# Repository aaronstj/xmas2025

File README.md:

# xmas2025

This is the code and schematics/PCB design for the 2025 Christmas ornament.

The ornament runs on an ATTINY85 microcontroller running the Micronucleus bootloader.  The code runs on the Arduino platform using the ATTinyCore.

## The top of the ornament looks like a USB?
It is! You can reprogram the ornament through the usb.  Download the ATTinyCore for Arduino, set your board to "ATTiny85 (Micronucleus/Digispark)".  When uploading new code, insert the ESB end of the ornament into your USB port, component-side up - it's not quite the same right size, so it may take some wiggling and careful holding.  You will likely need to use `Zadig` to install the `libusbK` driver.

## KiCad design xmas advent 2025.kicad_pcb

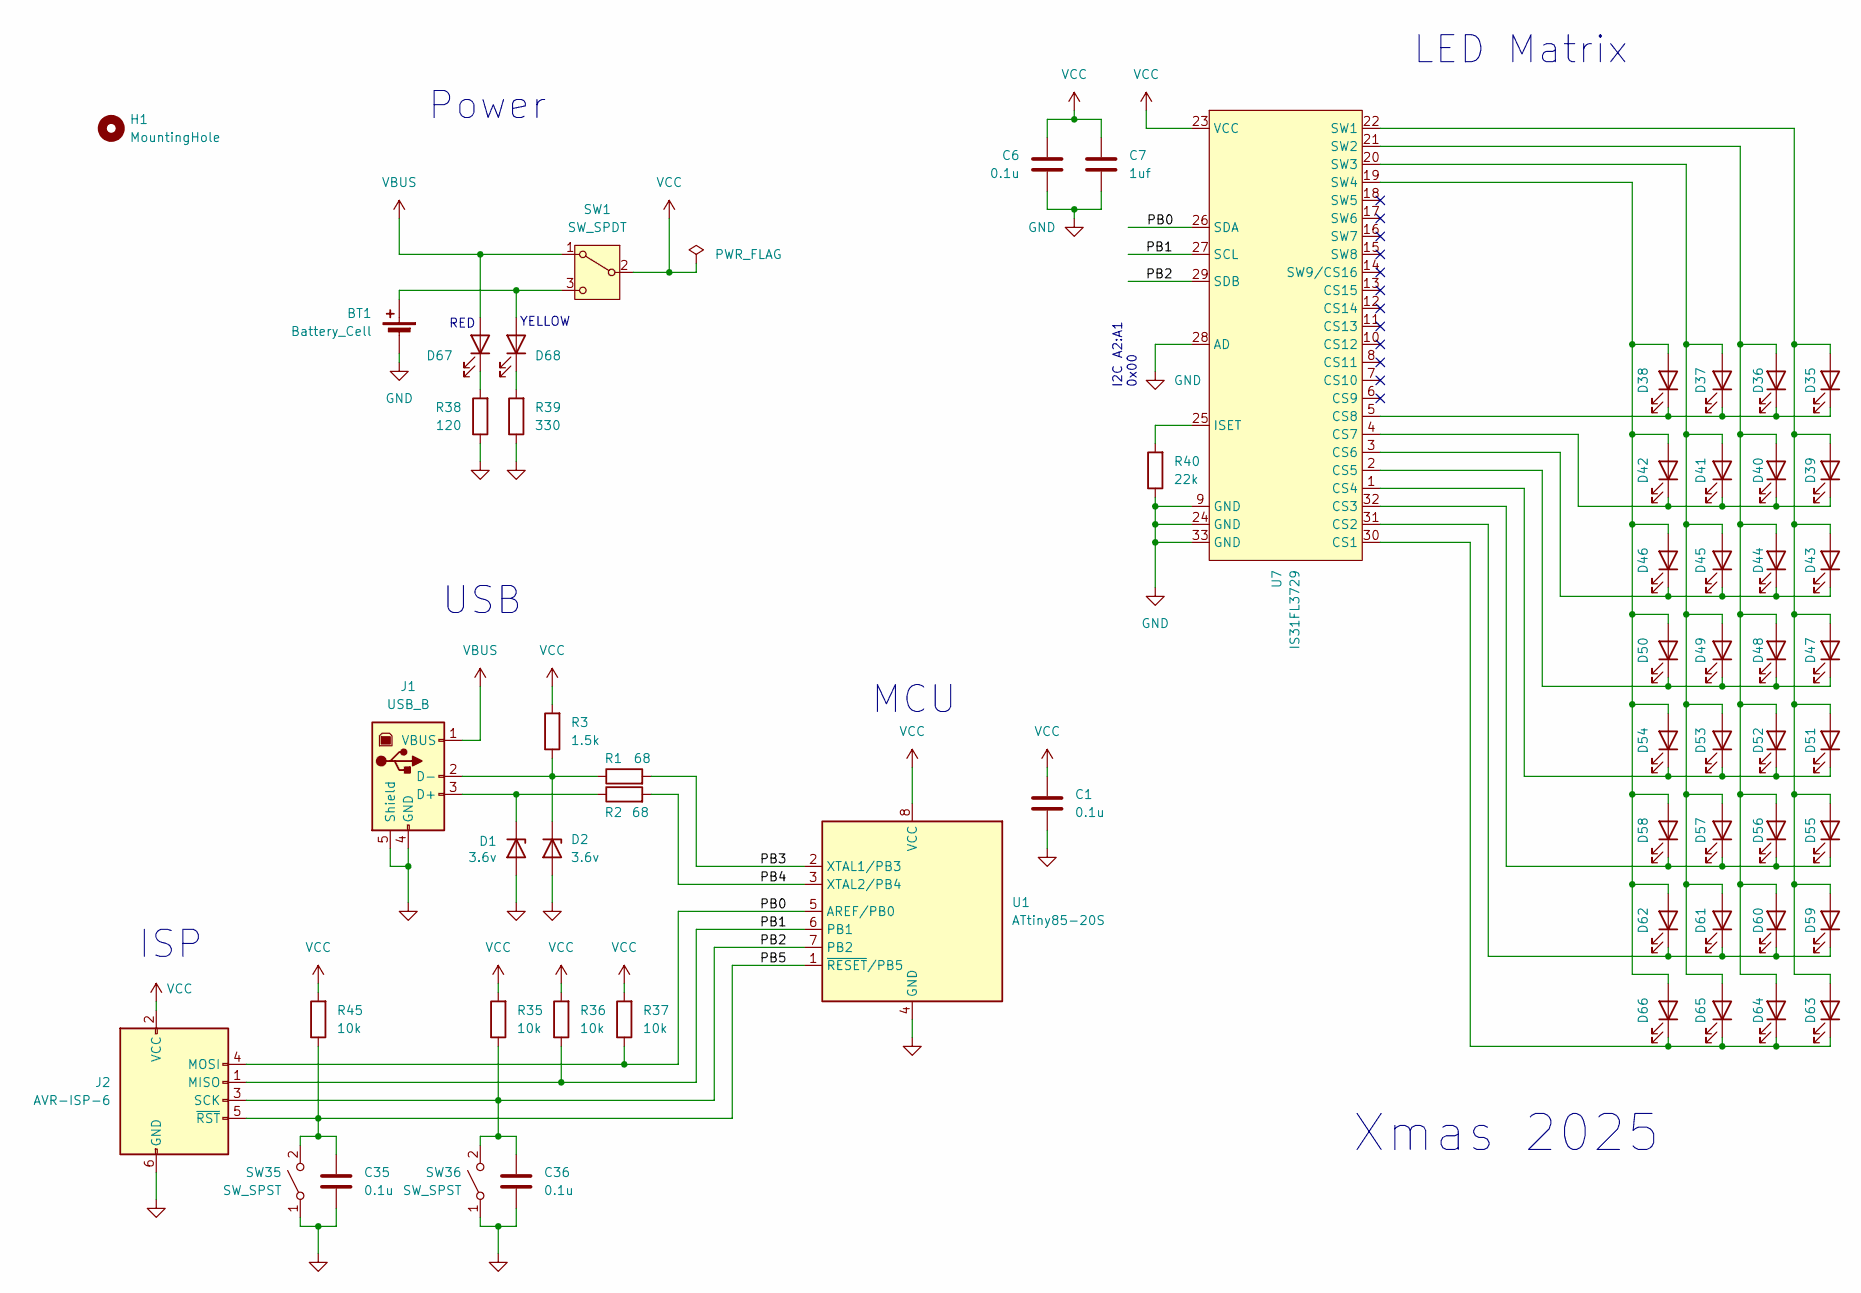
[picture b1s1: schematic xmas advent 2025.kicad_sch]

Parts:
BT1: Battery_Cell; BATTCOM_20MM_PTH
C1, C6, C35, C36: 0.1u; C_0402_1005Metric
C7: 1uf; C_0402_1005Metric
D1, D2: 3.6v; D_SOD-123
D35, D36, D37, D38, D39, D40, D41, D42, D43, D44, D45, D46, D47, D48, D49, D50, D51, D52, D53, D54, D55, D56, D57, D58, D59, D60, D61, D62, D63, D64, D65, D66: LED; LED_0805_2012Metric
D67: RED; LED_0603_1608Metric
D68: Yellow; LED_0603_1608Metric
H1: MountingHole; MountingHole_3mm
J1: USB_B; CONN-USB-A-PCB-TRACES
J2: AVR-ISP-6; PinHeader_2x03_P2.54mm_Vertical
R1, R2: 68; R_0402_1005Metric
R3: 1.5k; R_0402_1005Metric
R35, R36, R37, R45: 10k; R_0402_1005Metric
R38: 120; R_0402_1005Metric
R39: 330; R_0402_1005Metric
R40: 22k; R_0402_1005Metric
SW1: SW_SPDT; SW_500SSP1S2M2QEA
SW35, SW36: SW_SPST; SW_Push_1P1T_XKB_TS-1187A
U1: ATtiny85-20S; SOIC-8W_5.3x5.3mm_P1.27mm
U7: IS31FL3729; QFN-32-1EP_4x4mm_P0.4mm_EP2.65x2.65mm_ThermalVias

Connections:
/PB0: J2.4 (MOSI), R37.1, U1.5 (AREF/PB0), U7.26 (SDA)
/PB1: J2.1 (MISO), R36.1, U1.6 (PB1), U7.27 (SCL)
/PB2: C36.1, J2.3 (SCK), R35.1, SW36.2 (B), U1.7 (PB2), U7.29 (SDB)
/PB3: R1.2, U1.2 (XTAL1/PB3)
/PB4: R2.2, U1.3 (XTAL2/PB4)
/PB5: C35.1, J2.5 (~RST), R45.1, SW35.2 (B), U1.1 (~RESET/PB5)
GND: BT1.2 (-), C1.2, C6.1, C7.2, C35.2, C36.2, D1.2 (A), D2.2 (A), J1.4 (GND), J1.5 (Shield), J2.6 (GND), R38.1, R39.1, R40.1, SW35.1 (A), SW36.1 (A), U1.4 (GND), U7.9 (GND), U7.24 (GND), U7.28 (AD), U7.33 (GND)
unnamed: BT1.1 (+), D68.2 (A), SW1.3 (C)
unnamed: D1.1 (K), J1.3 (D+), R2.1
unnamed: D2.1 (K), J1.2 (D-), R1.1, R3.1
unnamed: D35.2 (A), D39.2 (A), D43.2 (A), D47.2 (A), D51.2 (A), D55.2 (A), D59.2 (A), D63.2 (A), U7.22 (SW1)
unnamed: D35.1 (K), D36.1 (K), D37.1 (K), D38.1 (K), U7.5 (CS8)
unnamed: D36.2 (A), D40.2 (A), D44.2 (A), D48.2 (A), D52.2 (A), D56.2 (A), D60.2 (A), D64.2 (A), U7.21 (SW2)
unnamed: D37.2 (A), D41.2 (A), D45.2 (A), D49.2 (A), D53.2 (A), D57.2 (A), D61.2 (A), D65.2 (A), U7.20 (SW3)
unnamed: D38.2 (A), D42.2 (A), D46.2 (A), D50.2 (A), D54.2 (A), D58.2 (A), D62.2 (A), D66.2 (A), U7.19 (SW4)
unnamed: D39.1 (K), D40.1 (K), D41.1 (K), D42.1 (K), U7.4 (CS7)
unnamed: D43.1 (K), D44.1 (K), D45.1 (K), D46.1 (K), U7.3 (CS6)
unnamed: D47.1 (K), D48.1 (K), D49.1 (K), D50.1 (K), U7.2 (CS5)
unnamed: D51.1 (K), D52.1 (K), D53.1 (K), D54.1 (K), U7.1 (CS4)
unnamed: D55.1 (K), D56.1 (K), D57.1 (K), D58.1 (K), U7.32 (CS3)
unnamed: D59.1 (K), D60.1 (K), D61.1 (K), D62.1 (K), U7.31 (CS2)
unnamed: D63.1 (K), D64.1 (K), D65.1 (K), D66.1 (K), U7.30 (CS1)
unnamed: D67.1 (K), R38.2
unnamed: D68.1 (K), R39.2
unnamed: R40.2, U7.25 (ISET)
VBUS: D67.2 (A), J1.1 (VBUS), SW1.1 (A)
VCC: C1.1, C6.2, C7.1, J2.2 (VCC), R3.2, R35.2, R36.2, R37.2, R45.2, SW1.2 (B), U1.8 (VCC), U7.23 (VCC)

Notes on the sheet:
USB
Power
LED Matrix
ISP
YELLOW
RED
Xmas 2025
I2C A2:A1 0x00
MCU

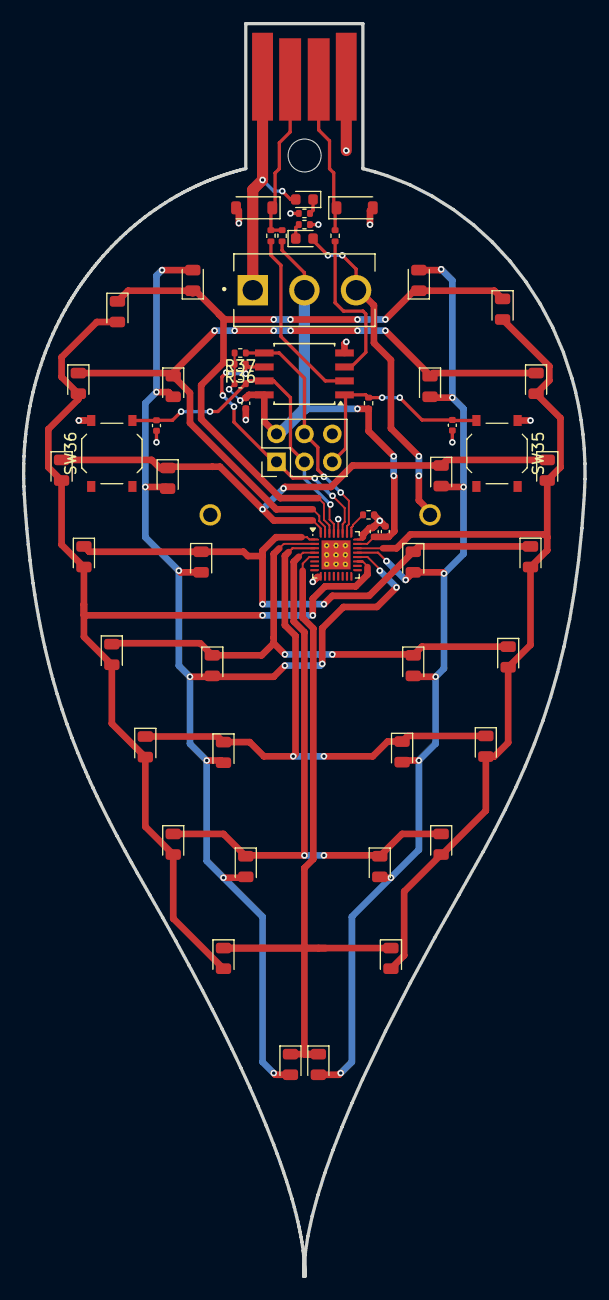
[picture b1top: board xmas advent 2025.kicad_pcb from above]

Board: 2 copper layers, 51.1 x 114.0 mm, 60 parts (1 on the bottom side), 27 nets.

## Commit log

2025-12-01 Initial README.md
2025-12-03 Update readme, raname arduino sketch
